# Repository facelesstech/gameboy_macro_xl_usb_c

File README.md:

# gameboy_macro_xl_usb_c
gameboy_macro_xl_usb_c

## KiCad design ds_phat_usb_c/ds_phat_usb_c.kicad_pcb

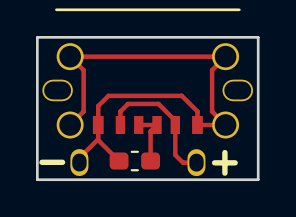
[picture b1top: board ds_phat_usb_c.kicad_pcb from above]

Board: 2 copper layers, 12.3 x 7.9 mm, 4 parts (0 on the bottom side), 3 nets.

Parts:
R1: R; R_0603_1608Metric_Pad1.05x0.95mm_HandSolder
U1: usb_c_6pin; USB_C_6PIN_custom
U2: battery_custom; ds_phat_charger_pins
U3: ds_charger_posts

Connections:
unnamed: R1.1, U1.3, U1.4
unnamed: R1.2, U1.1, U2.1
unnamed: U1.2, U2.2

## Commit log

2021-07-12 kicad files
2024-01-24 added 3d print stl for the usb c cover
